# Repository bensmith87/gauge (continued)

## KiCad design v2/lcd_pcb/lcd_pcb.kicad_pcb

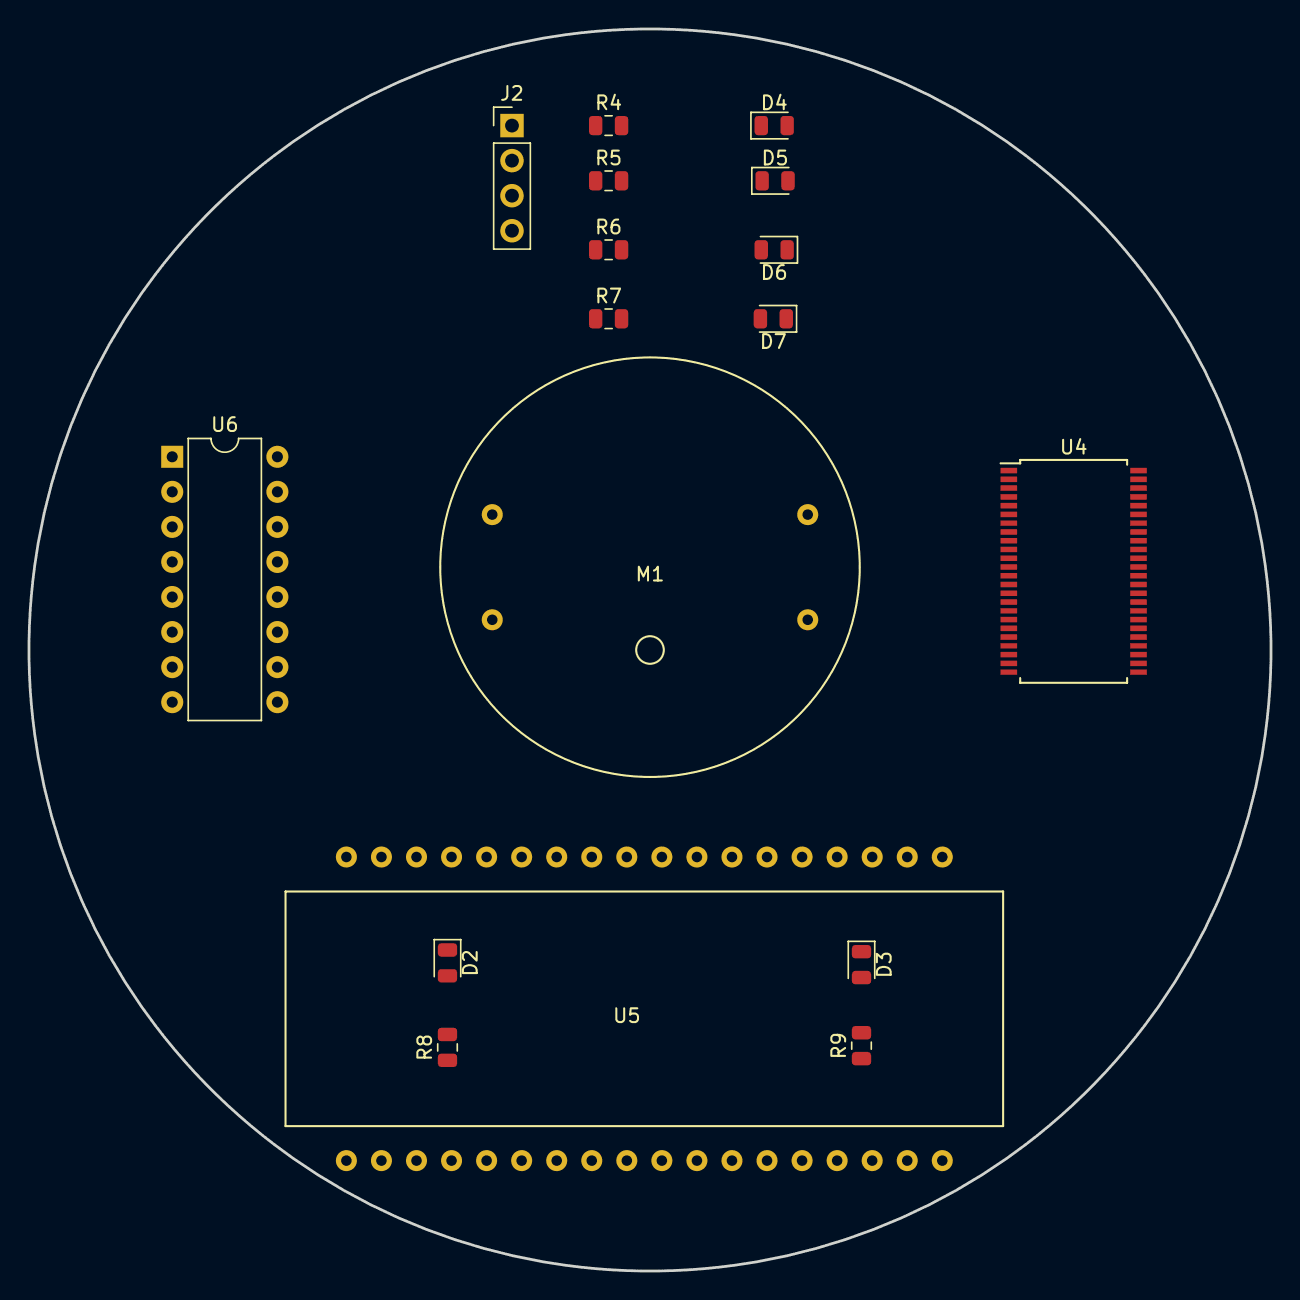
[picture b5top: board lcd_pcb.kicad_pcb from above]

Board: 2 copper layers, 90.0 x 90.0 mm, 17 parts (0 on the bottom side), 50 nets, no tracks yet.

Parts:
D2, D3, D4, D5, D6, D7: LED; LED_0805_2012Metric
J2: LEDS; PinHeader_1x04_P2.54mm_Vertical
M1: Stepper_Motor_bipolar; Stepper Motor
R4, R5, R6, R7: 220; R_0805_2012Metric
R8, R9: R; R_0805_2012Metric
U4: HT1621B; SSOP-48_7.5x15.9mm_P0.635mm
U5: VIM-878; VIM-878-DP
U6: L293D; DIP-16_W7.62mm

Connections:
+5V: D4.2, D5.2, R8.1, R9.1, U4.17, U6.1, U6.8, U6.9, U6.16
/COM0: U4.21, U5.17
/COM1: U4.22, U5.18
/COM2: U4.23, U5.19
/COM3: U4.24, U5.20
/SEG0: U4.8, U5.1
/SEG1: U4.7, U5.2
/SEG2: U4.6, U5.3
/SEG3: U4.5, U5.4
/SEG4: U4.4, U5.5
/SEG5: U4.3, U5.6
/SEG6: U4.2, U5.7
/SEG7: U4.1, U5.8
/SEG8: U4.48, U5.9
/SEG9: U4.47, U5.10
/SEG10: U4.46, U5.11
/SEG11: U4.45, U5.12
/SEG12: U4.44, U5.13
/SEG13: U4.43, U5.14
/SEG14: U4.42, U5.15
/SEG15: U4.41, U5.16
/SEG16: U4.40, U5.34
/SEG17: U4.39, U5.33
/SEG18: U4.38, U5.32
/SEG19: U4.37, U5.31
/SEG20: U4.36, U5.30
/SEG21: U4.35, U5.29
/SEG22: U4.34, U5.28
/SEG23: U4.33, U5.27
/SEG24: U4.32, U5.26
/SEG25: U4.31, U5.25
/SEG26: U4.30, U5.24
/SEG27: U4.29, U5.23
/SEG28: U4.28, U5.22
/SEG29: U4.27, U5.21
GND: D2.1, D3.1, D6.1, D7.1, U4.13, U6.4, U6.5, U6.12, U6.13
unnamed: D2.2, R8.2
unnamed: D3.2, R9.2
unnamed: D4.1, R4.2
unnamed: D5.1, R5.2
unnamed: D6.2, R6.2
unnamed: D7.2, R7.2
unnamed: J2.1, R4.1
unnamed: J2.2, R5.1
unnamed: J2.3, R6.1
unnamed: J2.4, R7.1
unnamed: M1.1, U6.6
unnamed: M1.2, U6.3
unnamed: M1.3, U6.11
unnamed: M1.4, U6.14

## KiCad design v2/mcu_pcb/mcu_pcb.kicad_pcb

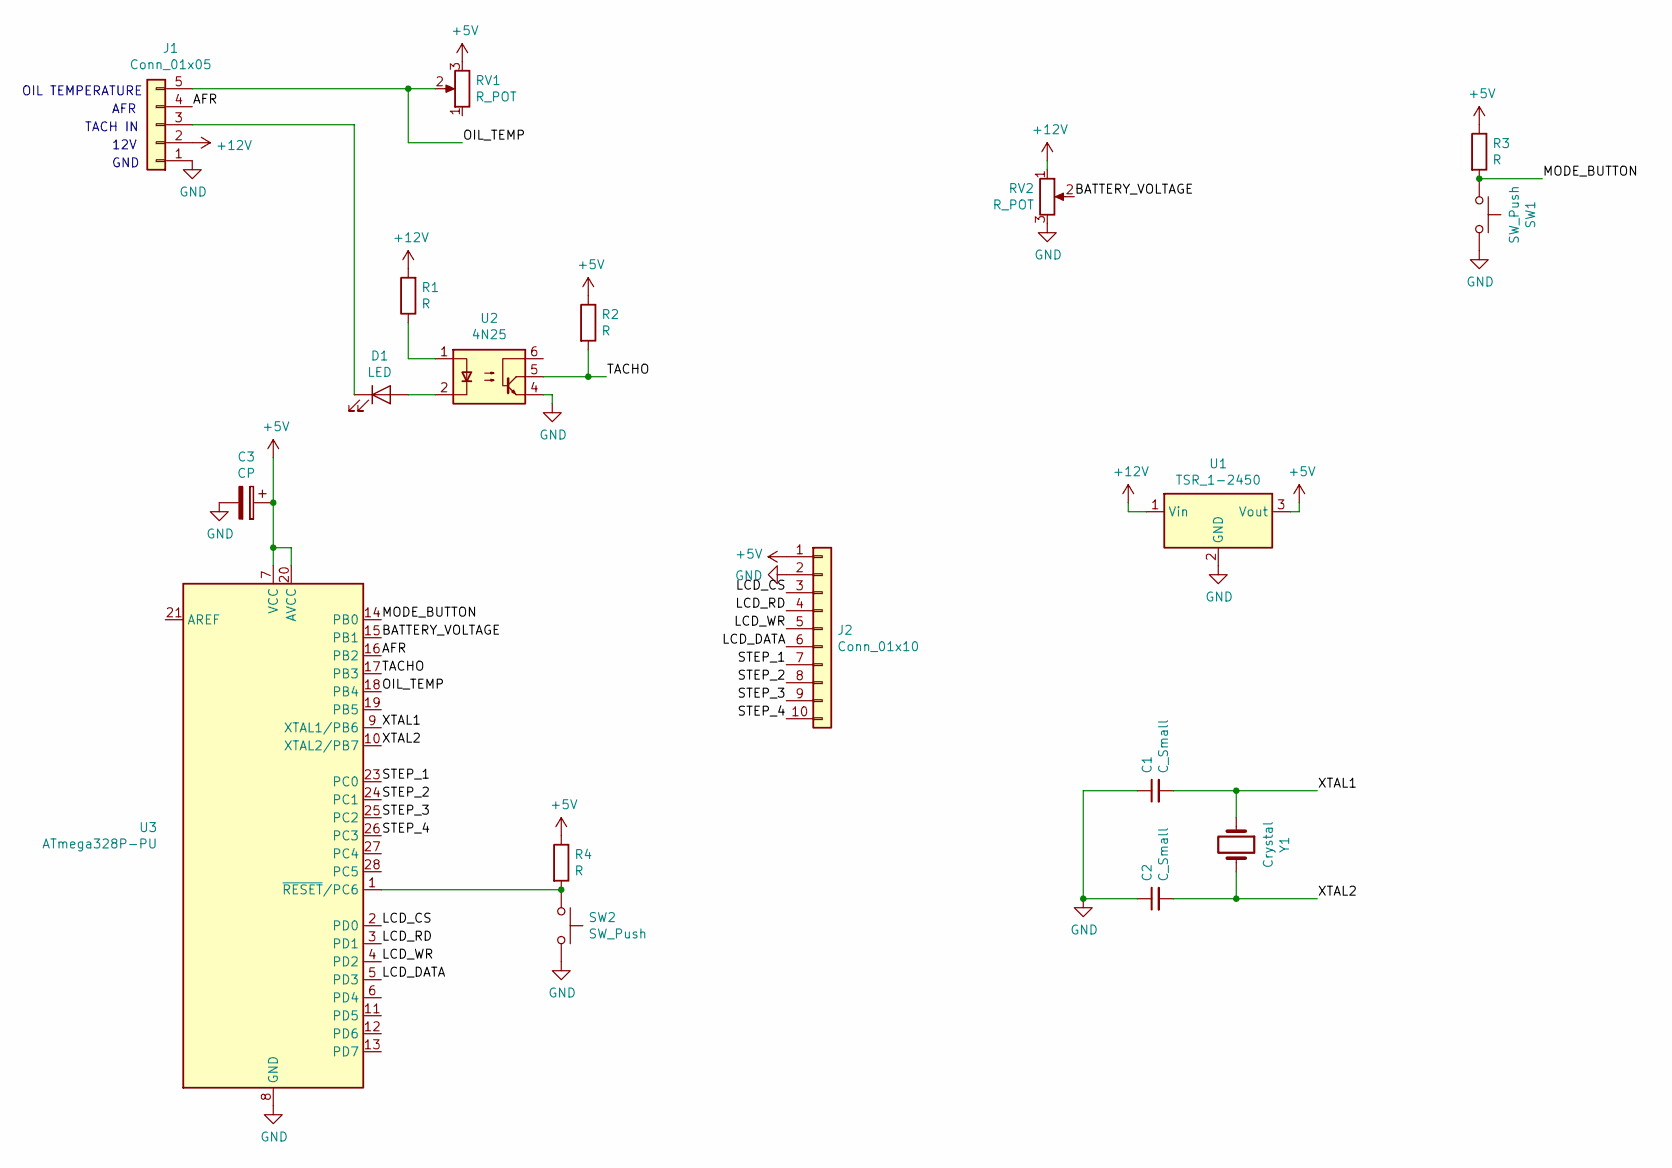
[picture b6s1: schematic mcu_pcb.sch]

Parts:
C1, C2: C_Small; C_Disc_D3.0mm_W1.6mm_P2.50mm
C3: CP; CP_Radial_D4.0mm_P1.50mm
D1: LED; LED_0805_2012Metric
J1: Conn_01x05; Molex_PicoBlade_53047-1010_1x05_P1.25mm_Vertical
J2: Conn_01x10; Molex_PicoBlade_53047-2010_1x10_P1.25mm_Vertical
R1, R2, R3, R4: R; R_0805_2012Metric
RV1, RV2: R_POT; Potentiometer_Bourns_3266Y_Vertical
SW1: SW_Push; SolderWirePad_1x02_P3.81mm_Drill1mm
SW2: SW_Push; SW_SPST_B3S-1000
U1: TSR_1-2450; Converter_DCDC_TRACO_TSR-1_THT
U2: 4N25; DIP-6_W7.62mm
U3: ATmega328P-PU; DIP-28_W7.62mm
Y1: Crystal; Resonator-2Pin_W7.0mm_H2.5mm

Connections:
+5V: C3.1, J2.1, R2.1, R3.1, R4.1, RV1.3, U1.3 (Vout), U3.7 (VCC), U3.20 (AVCC)
+12V: J1.2, R1.2, RV2.1, U1.1 (Vin)
/AFR: J1.4, U3.16 (PB2)
/BATTERY_VOLTAGE: RV2.2, U3.15 (PB1)
/LCD_CS: J2.3, U3.2 (PD0)
/LCD_DATA: J2.6, U3.5 (PD3)
/LCD_RD: J2.4, U3.3 (PD1)
/LCD_WR: J2.5, U3.4 (PD2)
/MODE_BUTTON: R3.2, SW1.1, U3.14 (PB0)
/OIL_TEMP: J1.5, RV1.2, U3.18 (PB4)
/STEP_1: J2.7, U3.23 (PC0)
/STEP_2: J2.8, U3.24 (PC1)
/STEP_3: J2.9, U3.25 (PC2)
/STEP_4: J2.10, U3.26 (PC3)
/TACHO: R2.2, U2.5, U3.17 (PB3)
/XTAL1: C1.2, U3.9 (XTAL1/PB6), Y1.1
/XTAL2: C2.2, U3.10 (XTAL2/PB7), Y1.2
GND: C1.1, C2.1, C3.2, J1.1, J2.2, RV2.3, SW1.2, SW2.2, U1.2 (GND), U2.4, U3.8 (GND), U3.22 (GND)
unnamed: D1.1 (K), J1.3
unnamed: D1.2 (A), U2.2
unnamed: R1.1, U2.1
unnamed: R4.2, SW2.1, U3.1 (~RESET~/PC6)

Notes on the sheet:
TACH IN
12V
GND
AFR
OIL TEMPERATURE

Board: 2 copper layers, 18 parts (0 on the bottom side), 22 nets, no tracks yet.

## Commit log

2019-04-26 Added fusion 360 model
2019-04-26 Tacho
2019-04-26 Tacho pulse period instead of pulse count
2019-04-26 Tacho stepper acceleration
2019-04-27 Stuff
2019-05-09 v1 and v2
2019-07-04 LCD version only
2019-07-13 Removed contrast pot and renamed segment nets
2019-07-13 Fixed LCD footprint
2019-07-13 Added missing segments
2019-07-13 Removed unused LCD read net
